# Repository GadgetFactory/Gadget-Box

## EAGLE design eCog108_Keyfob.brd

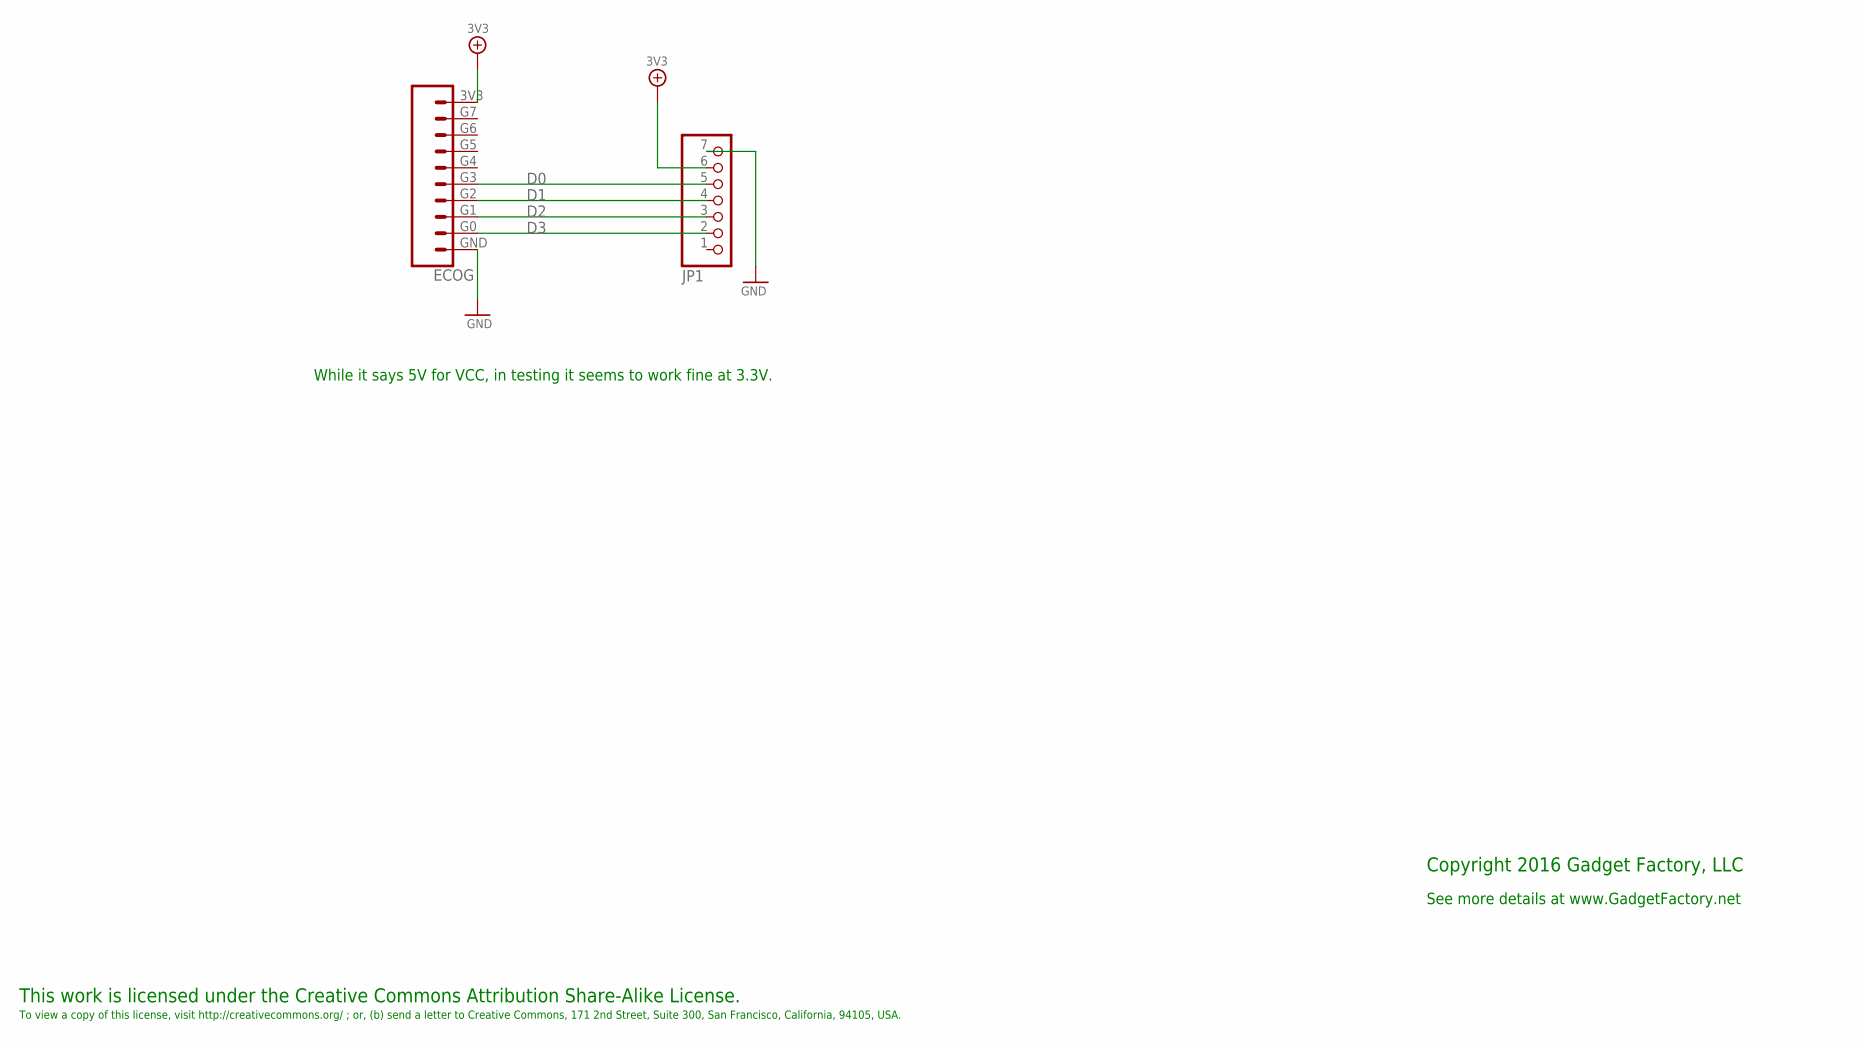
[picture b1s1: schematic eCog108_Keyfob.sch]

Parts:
ECOG: ECOG_GENERAL_ROWECOG_GENERAL_SMD; ECOG_GENERAL_SMD
JP1: PINHD-1X7; 1X07

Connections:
3V3: ECOG.3V3, JP1.6
D0: ECOG.G3, JP1.5
D1: ECOG.G2, JP1.4
D2: ECOG.G1, JP1.3
D3: ECOG.G0, JP1.2
GND: ECOG.GND, JP1.7

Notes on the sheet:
This work is licensed under the Creative Commons Attribution Share-Alike License.
To view a copy of this license, visit http://creativecommons.org/ ; or, (b) send a letter to Creative Commons, 171 2nd Street, Suite 300, San Francisco, California, 94105, USA.
Copyright 2016 Gadget Factory, LLC
See more details at www.GadgetFactory.net
While it says 5V for VCC, in testing it seems to work fine at 3.3V.

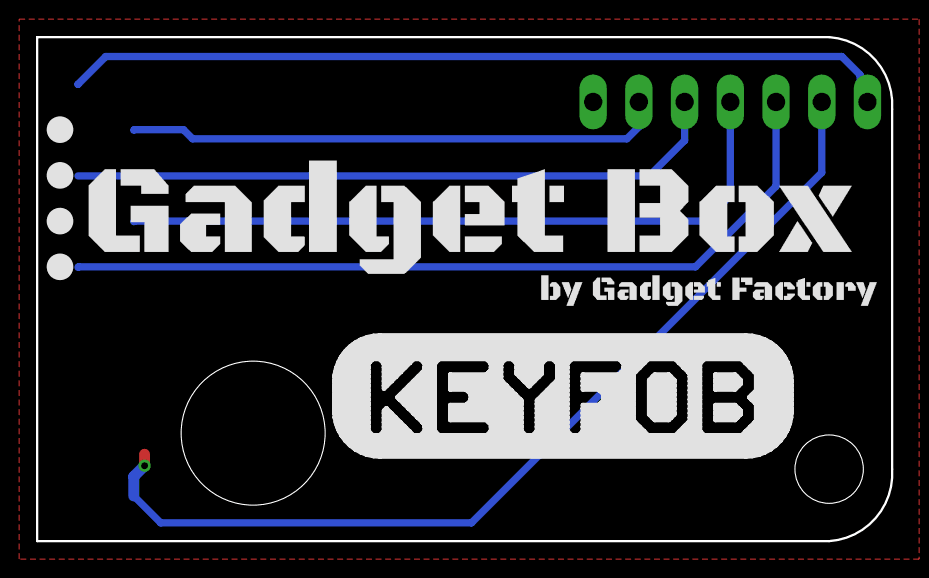
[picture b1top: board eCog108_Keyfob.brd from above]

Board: 2 copper layers, 47.5 x 28.0 mm, 7 parts (0 on the bottom side), 6 nets.

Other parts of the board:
U$1: GADGETBOX_TEXT
U$2, U$3, U$4, U$5: LEGEND_DIO

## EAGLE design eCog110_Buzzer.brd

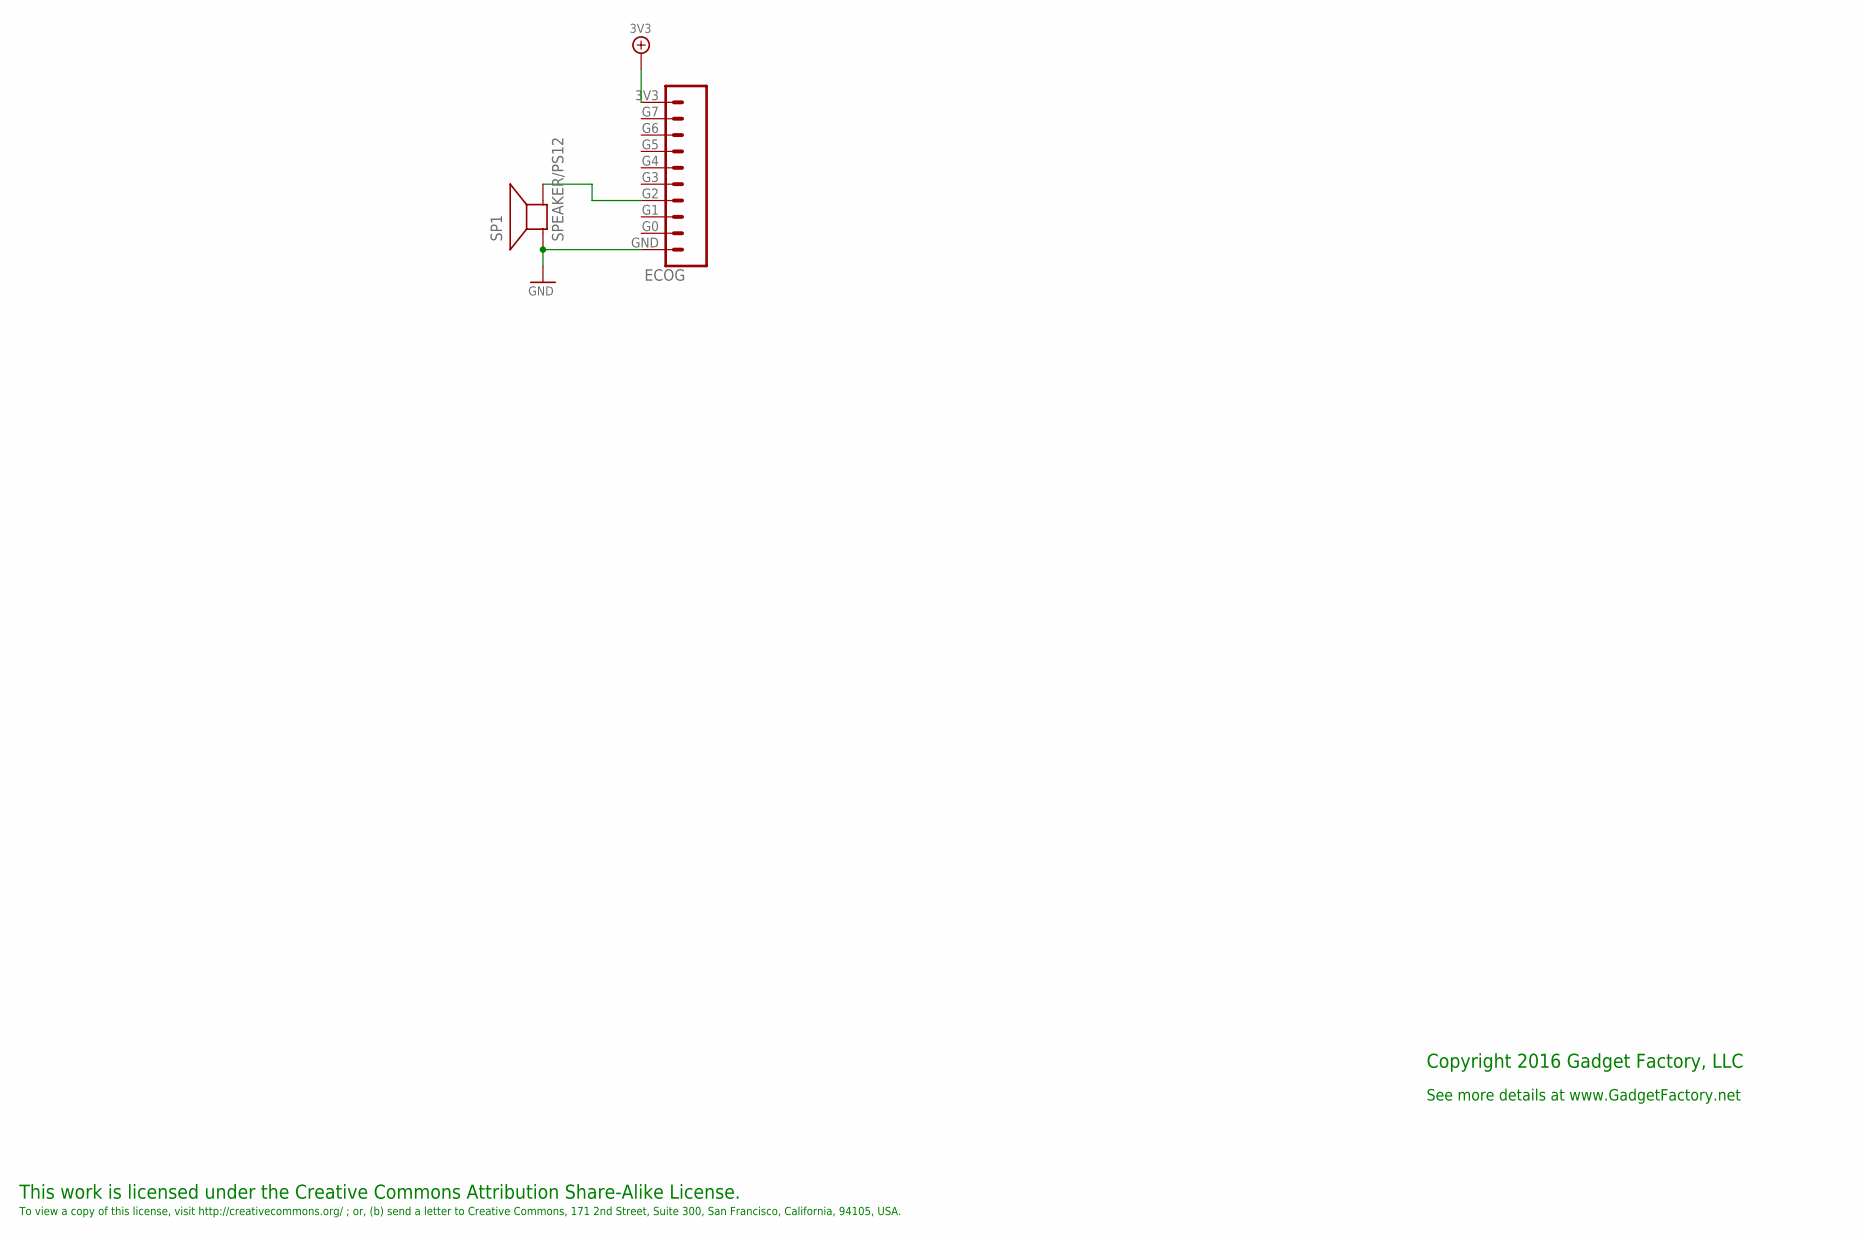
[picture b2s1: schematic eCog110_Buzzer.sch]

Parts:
ECOG: ECOG_GENERAL_ROWECOG_GENERAL_SMD; ECOG_GENERAL_SMD; PARTNO NREC010SABC-M30RC,SULLINS CONNECTOR SOL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
SP1: SPEAKER/PS12; PS12; PARTNO PS1240P02BT,TDK CORPORATION (VA),dk,445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; DIGIKEY 445-2525-1-ND

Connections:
3V3: ECOG.3V3
GND: ECOG.GND, SP1.P$1 (+)
unnamed: ECOG.G2, SP1.P$2 (-)

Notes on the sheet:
This work is licensed under the Creative Commons Attribution Share-Alike License.
To view a copy of this license, visit http://creativecommons.org/ ; or, (b) send a letter to Creative Commons, 171 2nd Street, Suite 300, San Francisco, California, 94105, USA.
Copyright 2016 Gadget Factory, LLC
See more details at www.GadgetFactory.net

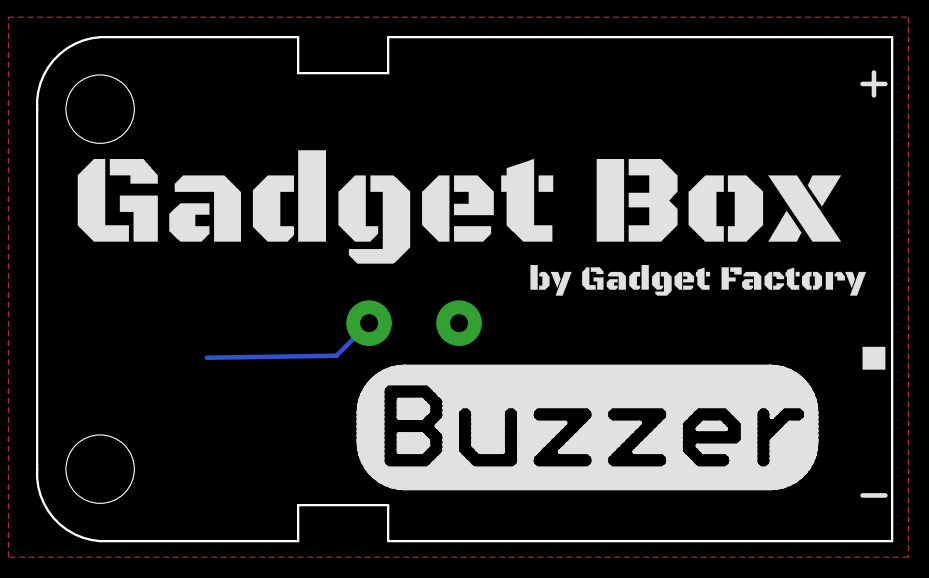
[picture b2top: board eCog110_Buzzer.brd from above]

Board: 2 copper layers, 47.5 x 28.0 mm, 4 parts (1 on the bottom side), 2 nets.

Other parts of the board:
U$1: GADGETBOX_TEXT
U$4: LEGEND_PWM

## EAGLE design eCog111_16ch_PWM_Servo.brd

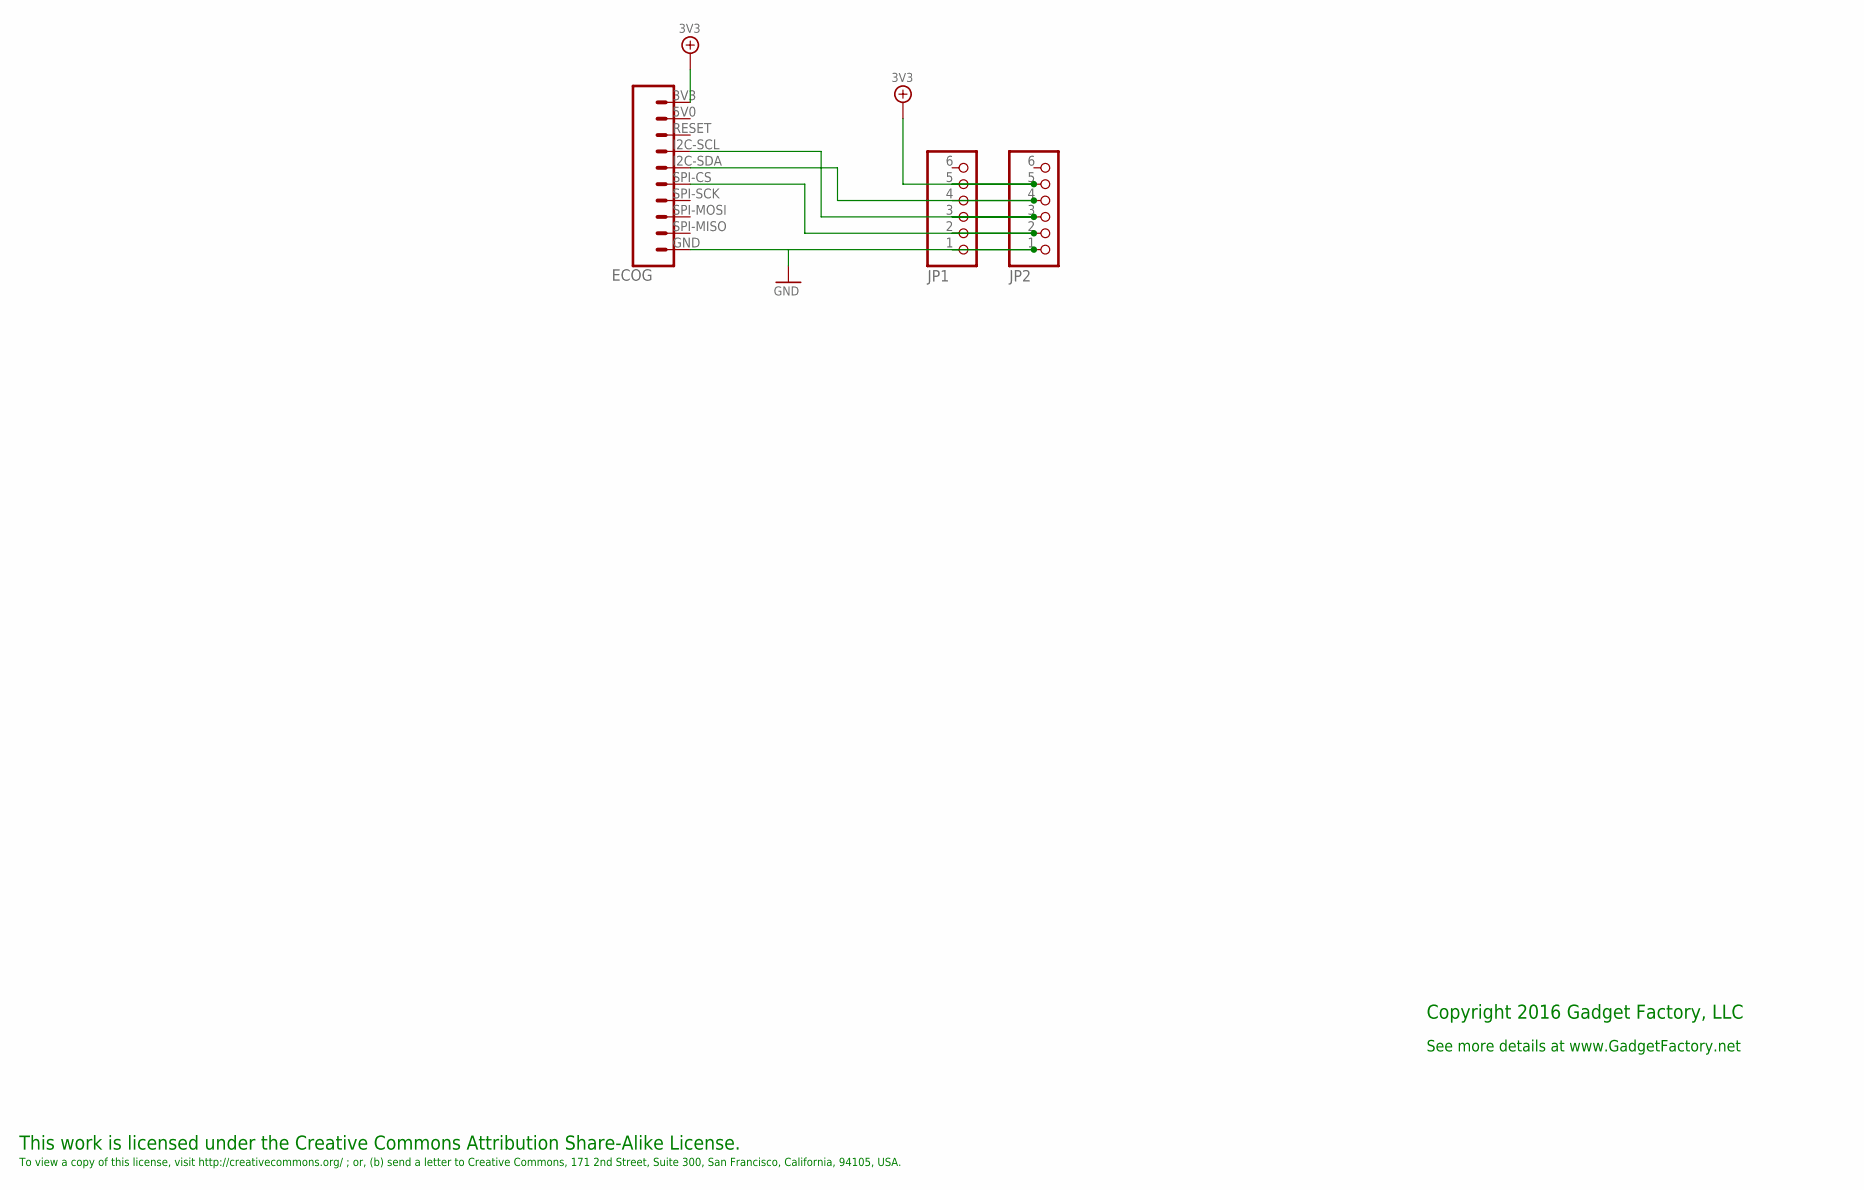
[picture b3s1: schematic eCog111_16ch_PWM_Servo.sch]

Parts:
ECOG: ECOG_BUSES_ROWECOG_BUSES_SMD; ECOG_BUSES_SMD
JP1, JP2: PINHD-1X6; 1X06

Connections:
3V3: ECOG.3V3, JP1.5, JP2.5
GND: ECOG.GND, JP1.1, JP2.1
unnamed: ECOG.SPI-CS, JP1.2, JP2.2
unnamed: ECOG.I2C-SCL, JP1.3, JP2.3
unnamed: ECOG.I2C-SDA, JP1.4, JP2.4

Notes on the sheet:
This work is licensed under the Creative Commons Attribution Share-Alike License.
To view a copy of this license, visit http://creativecommons.org/ ; or, (b) send a letter to Creative Commons, 171 2nd Street, Suite 300, San Francisco, California, 94105, USA.
Copyright 2016 Gadget Factory, LLC
See more details at www.GadgetFactory.net

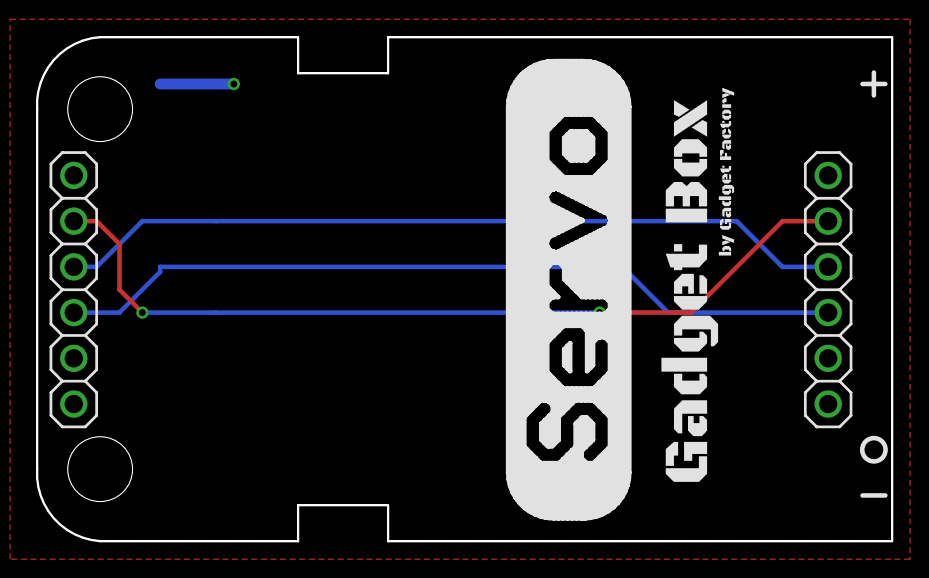
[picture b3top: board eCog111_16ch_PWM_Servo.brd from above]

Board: 2 copper layers, 47.5 x 28.0 mm, 4 parts (0 on the bottom side), 5 nets.

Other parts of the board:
U$2: GADGETBOX_SMALL

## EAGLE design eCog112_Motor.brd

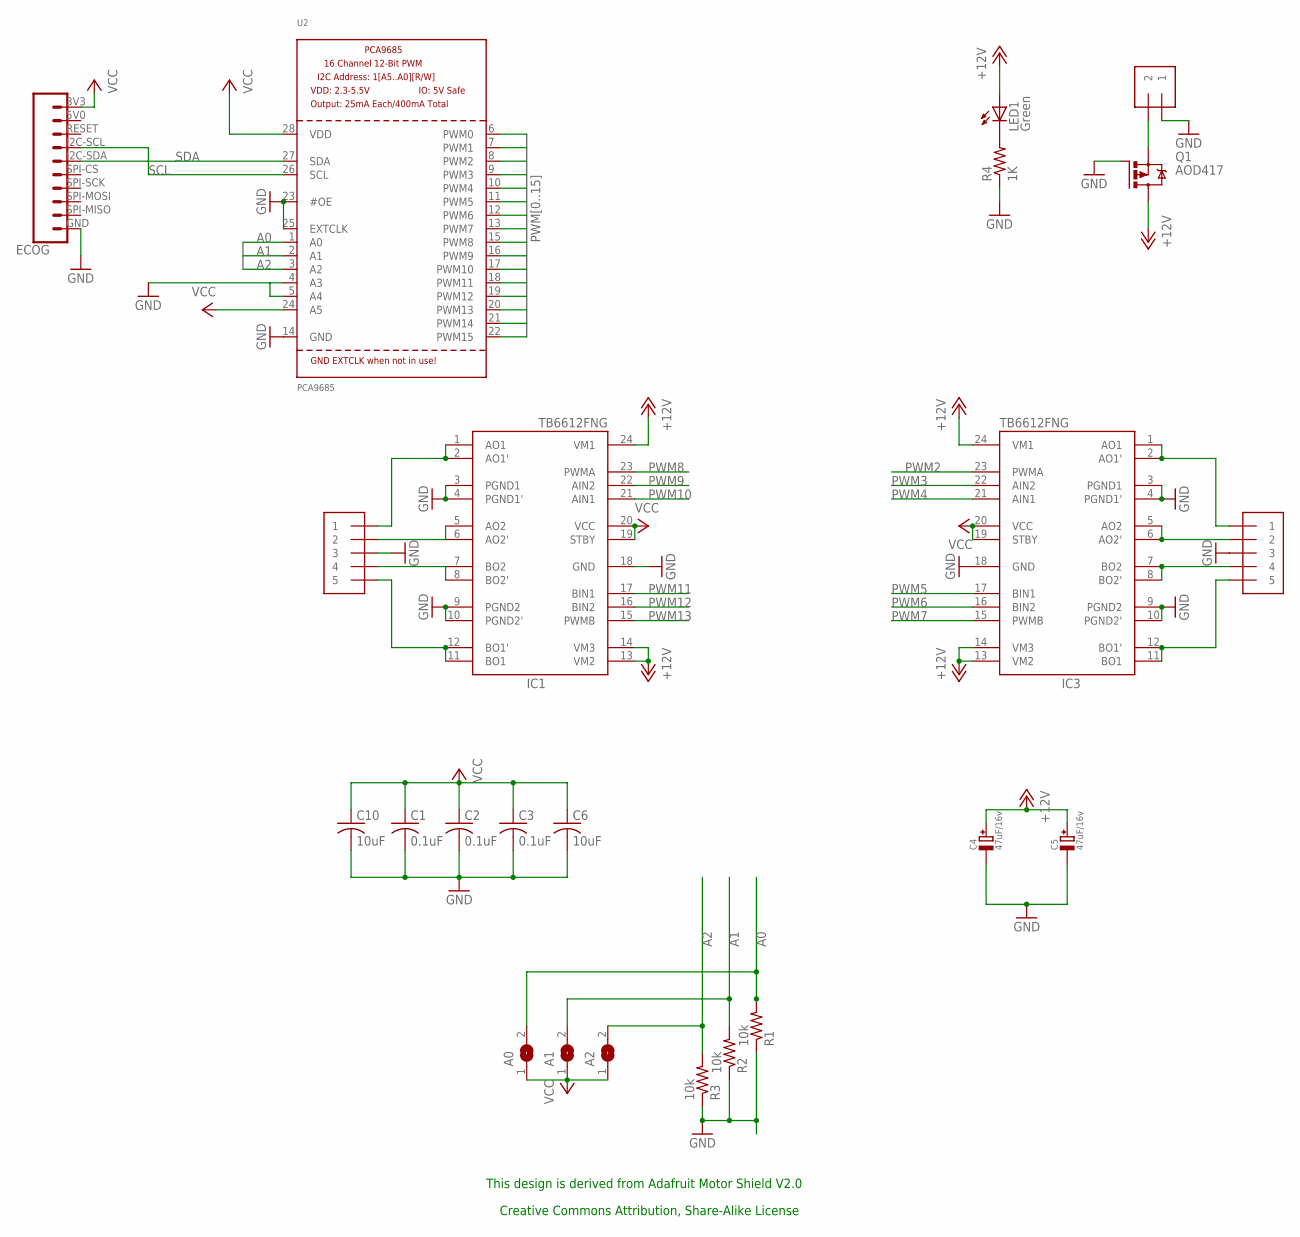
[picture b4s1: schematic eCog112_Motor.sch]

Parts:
A0, A1, A2: SJ
C1, C2, C3: 0.1uF; C0603; PARTNO GRM188F51E104ZA01D,MURATA ELECTRONICS (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
C4, C5: 47uF/16v; PANASONIC_C; PARTNO EEE-1CA470WR,panasonic,dk,PCE3890CT-ND 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; DIGIKEY PCE3890CT-ND
C6, C10: 10uF; C0603; PARTNO GRM188R60G106ME47D,MURATA ELECTRONICS (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
ECOG: ECOG_BUSES_ROWECOG_BUSES_SMD; ECOG_BUSES_SMD; PARTNO NREC010SABC-M30RC,SULLINS CONNECTOR SOL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
IC1, IC3: TB6612FNG; SSOP24; PARTNO TB6612FNGC8EL,Toshiba,dk,TB6612FNGC8ELC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
J1, J2: 1X5; 1X05-3.5MM; PARTNO 1984646,Pheonix Contact,dk,277-1723-ND,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
LED1: Green; CHIP-LED0805; PARTNO LTST-C170KGKT,LITE-ON INC (VA),DK,160-1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
MPOWER: 1X2-3.5MM; PARTNO 1984617,Pheonix Contact,dk,277-1721-ND,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
Q1: AOD417; D-PAK_TO252AA; PARTNO AOD417,Alpha & Omega Semiconductor Inc.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
R1, R2, R3: 10k; R0805; PARTNO RC0805JR-0710KL,YAGEO (VA),dk,311-10KAR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
R4: 1K; R0603; PARTNO RC0603JR-071KL,YAGEO (VA),dk,311-1.0KGR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
U2: PCA9685; TSSOP28; PARTNO PCA9685PWQ900118,NXP,dk,568-5931-1-ND,L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

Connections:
3V3: A0.1, A1.1, A2.1, C1.1, C2.1, C3.1, C6.1, C10.1, ECOG.3V3, IC1.19 (STBY), IC1.20 (VCC), IC3.19 (STBY), IC3.20 (VCC), U2.24 (A5), U2.28 (VDD)
+12V: C4.+, C5.+, IC1.13 (VM2), IC1.14 (VM3), IC1.24 (VM1), IC3.13 (VM2), IC3.14 (VM3), IC3.24 (VM1), LED1.A, Q1.4 (D)
A0: A0.2, R1.2, U2.1 (A0)
A1: A1.2, R2.2, U2.2 (A1)
A2: A2.2, R3.2, U2.3 (A2)
GND: C1.2, C2.2, C3.2, C4.-, C5.-, C6.2, C10.2, ECOG.GND, IC1.3 (PGND1), IC1.4 (PGND1'), IC1.9 (PGND2), IC1.10 (PGND2'), IC1.18 (GND), IC3.3 (PGND1), IC3.4 (PGND1'), IC3.9 (PGND2), IC3.10 (PGND2'), IC3.18 (GND), J1.3, J2.3, MPOWER.1, Q1.1 (G), R1.1, R2.1, R3.1, R4.1, U2.4 (A3), U2.5 (A4), U2.14 (GND), U2.23 (#OE), U2.25 (EXTCLK)
unnamed: IC1.1 (AO1), IC1.2 (AO1'), J1.1
unnamed: IC1.5 (AO2), IC1.6 (AO2'), J1.2
unnamed: IC1.7 (BO2), IC1.8 (BO2'), J1.4
unnamed: IC1.11 (BO1), IC1.12 (BO1'), J1.5
unnamed: IC3.1 (AO1), IC3.2 (AO1'), J2.1
unnamed: IC3.5 (AO2), IC3.6 (AO2'), J2.2
unnamed: IC3.7 (BO2), IC3.8 (BO2'), J2.4
unnamed: IC3.11 (BO1), IC3.12 (BO1'), J2.5
unnamed: LED1.C, R4.2
unnamed: MPOWER.2, Q1.3 (S)
PWM0: U2.6 (PWM0)
PWM1: U2.7 (PWM1)
PWM2: IC3.23 (PWMA), U2.8 (PWM2)
PWM3: IC3.22 (AIN2), U2.9 (PWM3)
PWM4: IC3.21 (AIN1), U2.10 (PWM4)
PWM5: IC3.17 (BIN1), U2.11 (PWM5)
PWM6: IC3.16 (BIN2), U2.12 (PWM6)
PWM7: IC3.15 (PWMB), U2.13 (PWM7)
PWM8: IC1.23 (PWMA), U2.15 (PWM8)
PWM9: IC1.22 (AIN2), U2.16 (PWM9)
PWM10: IC1.21 (AIN1), U2.17 (PWM10)
PWM11: IC1.17 (BIN1), U2.18 (PWM11)
PWM12: IC1.16 (BIN2), U2.19 (PWM12)
PWM13: IC1.15 (PWMB), U2.20 (PWM13)
PWM14: U2.21 (PWM14)
PWM15: U2.22 (PWM15)
SCL: ECOG.I2C-SCL, U2.26 (SCL)
SDA: ECOG.I2C-SDA, U2.27 (SDA)

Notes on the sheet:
This design is derived from Adafruit Motor Shield V2.0
Creative Commons Attribution, Share-Alike License

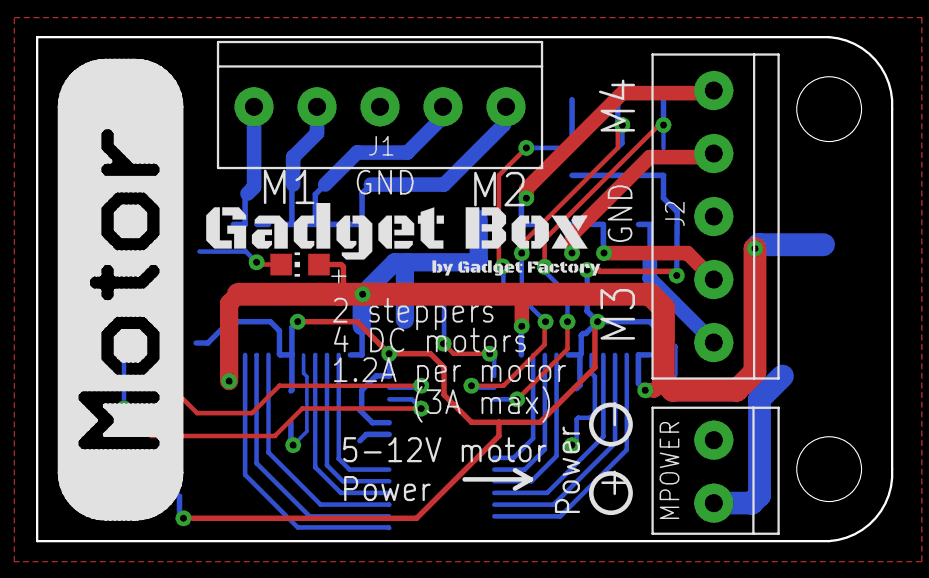
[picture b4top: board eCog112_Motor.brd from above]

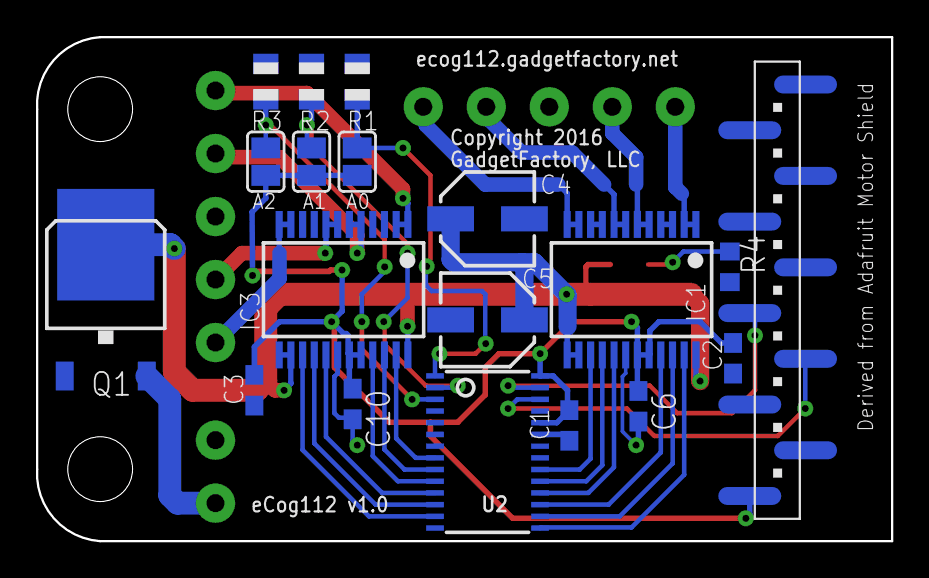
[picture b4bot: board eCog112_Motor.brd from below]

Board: 2 copper layers, 47.5 x 28.0 mm, 24 parts (18 on the bottom side), 30 nets.

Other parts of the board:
U$2: GADGETBOX_SMALL

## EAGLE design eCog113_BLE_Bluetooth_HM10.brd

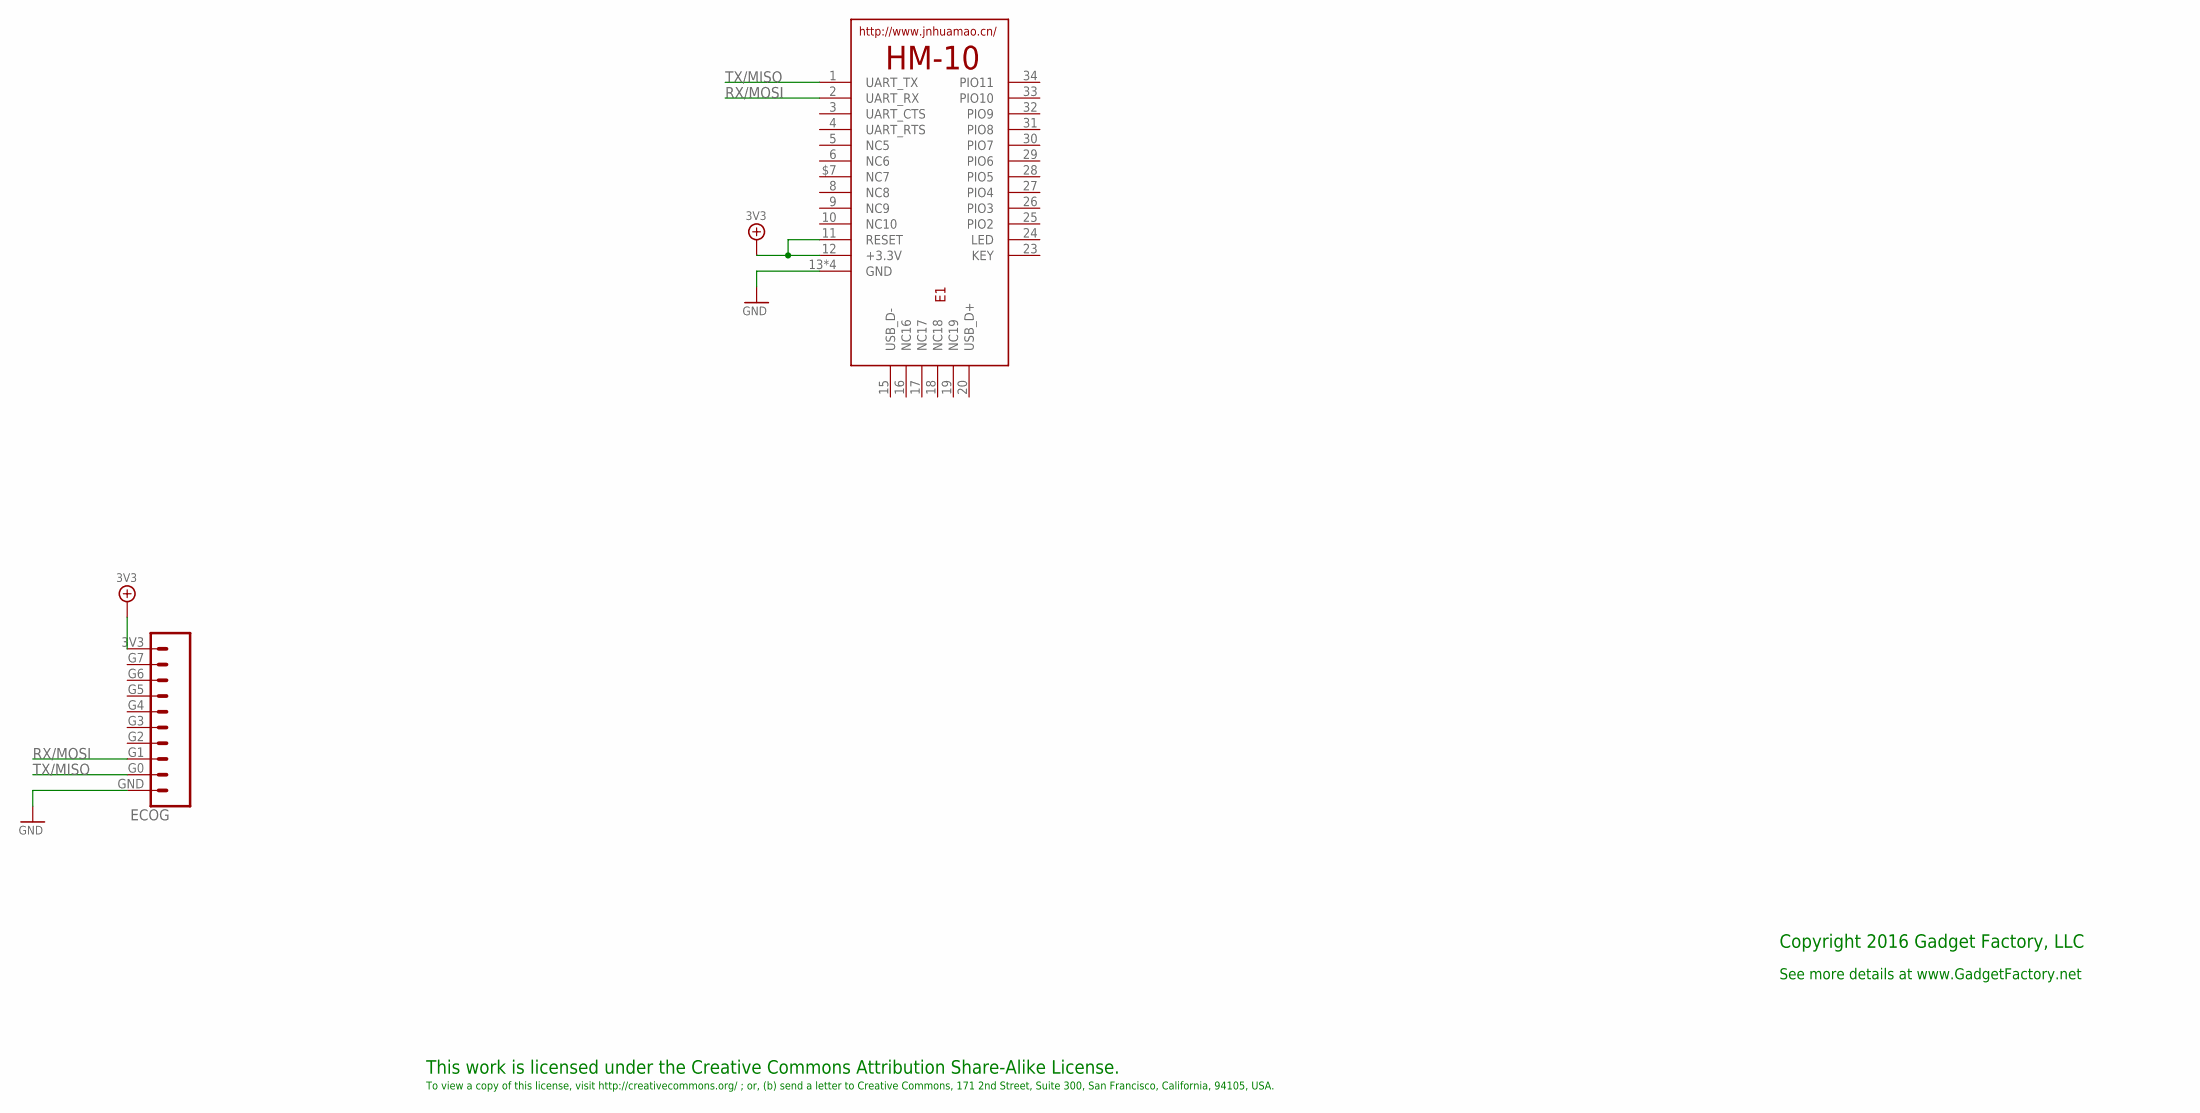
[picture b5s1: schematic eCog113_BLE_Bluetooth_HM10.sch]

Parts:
E1: HM-10-BOARD; 26.9X13X2.2_BOARD
ECOG: ECOG_GENERAL_ROWECOG_GENERAL_SMD; ECOG_GENERAL_SMD

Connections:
3V3: E1.11 (RESET), E1.12 (+3.3V), ECOG.3V3
GND: E1.13 (GND), E1.14 (GND), E1.21 (GND), E1.22 (GND), ECOG.GND
RX/MOSI: E1.2 (UART_RX), ECOG.G1
TX/MISO: E1.1 (UART_TX), ECOG.G0

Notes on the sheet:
This work is licensed under the Creative Commons Attribution Share-Alike License.
To view a copy of this license, visit http://creativecommons.org/ ; or, (b) send a letter to Creative Commons, 171 2nd Street, Suite 300, San Francisco, California, 94105, USA.
Copyright 2016 Gadget Factory, LLC
See more details at www.GadgetFactory.net

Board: 2 copper layers, 5 parts (1 on the bottom side), 4 nets.

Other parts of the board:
U$1: GADGETBOX_TEXT
U$2, U$3: LEGEND_DIO

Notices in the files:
parts and their libraries:
microbuilder: This work is placed in the public domain, and may be freely used for commercial and non-commercial work with the following conditions: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
